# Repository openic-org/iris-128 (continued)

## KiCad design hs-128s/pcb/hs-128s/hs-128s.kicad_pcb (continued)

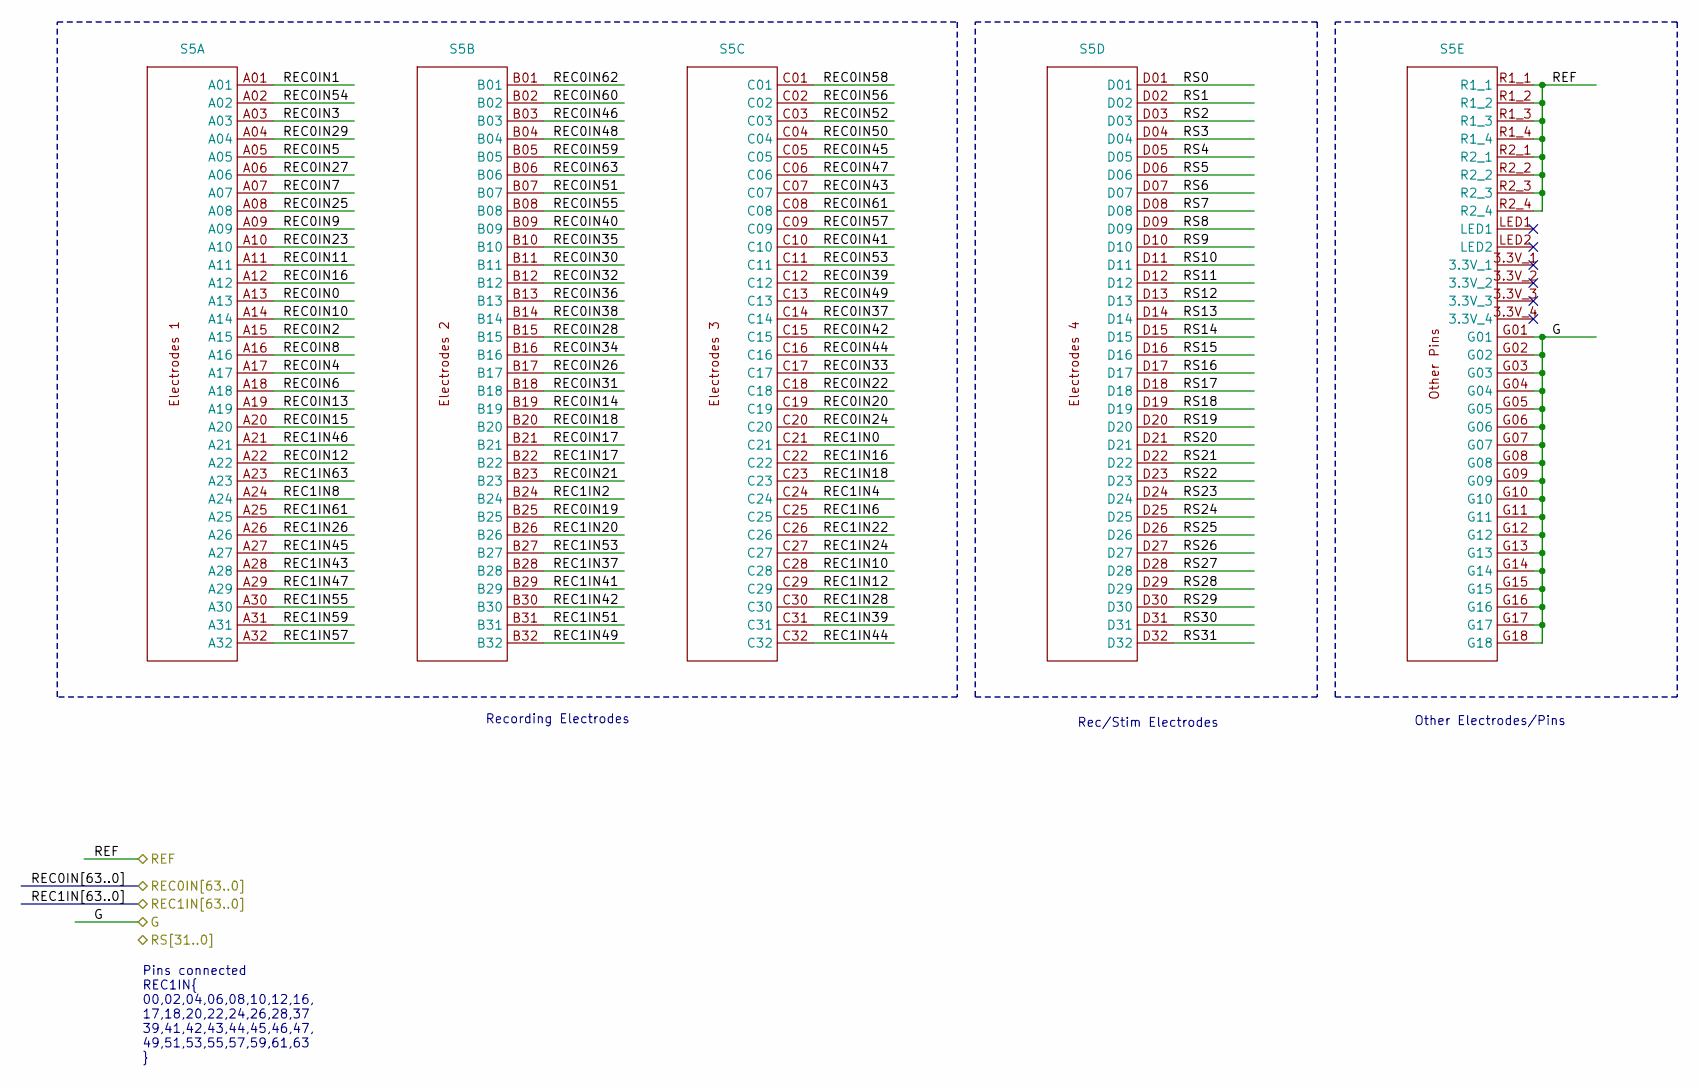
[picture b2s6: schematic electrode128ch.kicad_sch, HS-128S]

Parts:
S5: SAMTEC_SEAM8-20-S02.0-X-08-3_Cereplex; MPN SEAM8-20-S02.0-S-08-3

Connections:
/REC0IN0: S5.A13; also elsewhere on the board
/REC0IN1: S5.A01; also elsewhere on the board
/REC0IN2: S5.A15; also elsewhere on the board
/REC0IN3: S5.A03; also elsewhere on the board
/REC0IN4: S5.A17; also elsewhere on the board
/REC0IN5: S5.A05; also elsewhere on the board
/REC0IN6: S5.A18; also elsewhere on the board
/REC0IN7: S5.A07; also elsewhere on the board
/REC0IN8: S5.A16; also elsewhere on the board
/REC0IN9: S5.A09; also elsewhere on the board
/REC0IN10: S5.A14; also elsewhere on the board
/REC0IN11: S5.A11; also elsewhere on the board
/REC0IN12: S5.A22; also elsewhere on the board
/REC0IN13: S5.A19; also elsewhere on the board
/REC0IN14: S5.B19; also elsewhere on the board
/REC0IN15: S5.A20; also elsewhere on the board
/REC0IN16: S5.A12; also elsewhere on the board
/REC0IN17: S5.B21; also elsewhere on the board
/REC0IN18: S5.B20; also elsewhere on the board
/REC0IN19: S5.B25; also elsewhere on the board
/REC0IN20: S5.C19; also elsewhere on the board
/REC0IN21: S5.B23; also elsewhere on the board
/REC0IN22: S5.C18; also elsewhere on the board
/REC0IN23: S5.A10; also elsewhere on the board
/REC0IN24: S5.C20; also elsewhere on the board
/REC0IN25: S5.A08; also elsewhere on the board
/REC0IN26: S5.B17; also elsewhere on the board
/REC0IN27: S5.A06; also elsewhere on the board
/REC0IN28: S5.B15; also elsewhere on the board
/REC0IN29: S5.A04; also elsewhere on the board
/REC0IN30: S5.B11; also elsewhere on the board
/REC0IN31: S5.B18; also elsewhere on the board
/REC0IN32: S5.B12; also elsewhere on the board
/REC0IN33: S5.C17; also elsewhere on the board
/REC0IN34: S5.B16; also elsewhere on the board
/REC0IN35: S5.B10; also elsewhere on the board
/REC0IN36: S5.B13; also elsewhere on the board
/REC0IN37: S5.C14; also elsewhere on the board
/REC0IN38: S5.B14; also elsewhere on the board
/REC0IN39: S5.C12; also elsewhere on the board
/REC0IN40: S5.B09; also elsewhere on the board
/REC0IN41: S5.C10; also elsewhere on the board
/REC0IN42: S5.C15; also elsewhere on the board
/REC0IN43: S5.C07; also elsewhere on the board
/REC0IN44: S5.C16; also elsewhere on the board
/REC0IN45: S5.C05; also elsewhere on the board
/REC0IN46: S5.B03; also elsewhere on the board
/REC0IN47: S5.C06; also elsewhere on the board
/REC0IN48: S5.B04; also elsewhere on the board
/REC0IN49: S5.C13; also elsewhere on the board
/REC0IN50: S5.C04; also elsewhere on the board
/REC0IN51: S5.B07; also elsewhere on the board
/REC0IN52: S5.C03; also elsewhere on the board
/REC0IN53: S5.C11; also elsewhere on the board
/REC0IN54: S5.A02; also elsewhere on the board
/REC0IN55: S5.B08; also elsewhere on the board
/REC0IN56: S5.C02; also elsewhere on the board
/REC0IN57: S5.C09; also elsewhere on the board
/REC0IN58: S5.C01; also elsewhere on the board
/REC0IN59: S5.B05; also elsewhere on the board
/REC0IN60: S5.B02; also elsewhere on the board
/REC0IN61: S5.C08; also elsewhere on the board
/REC0IN62: S5.B01; also elsewhere on the board
/REC0IN63: S5.B06; also elsewhere on the board
/REC1IN0: S5.C21; also elsewhere on the board
/REC1IN2: S5.B24; also elsewhere on the board
/REC1IN4: S5.C24; also elsewhere on the board
/REC1IN6: S5.C25; also elsewhere on the board
/REC1IN8: S5.A24; also elsewhere on the board
/REC1IN10: S5.C28; also elsewhere on the board
/REC1IN12: S5.C29; also elsewhere on the board
/REC1IN16: S5.C22; also elsewhere on the board
/REC1IN17: S5.B22; also elsewhere on the board
/REC1IN18: S5.C23; also elsewhere on the board
/REC1IN20: S5.B26; also elsewhere on the board
/REC1IN22: S5.C26; also elsewhere on the board
/REC1IN24: S5.C27; also elsewhere on the board
/REC1IN26: S5.A26; also elsewhere on the board
/REC1IN28: S5.C30; also elsewhere on the board
/REC1IN37: S5.B28; also elsewhere on the board
/REC1IN39: S5.C31; also elsewhere on the board
/REC1IN41: S5.B29; also elsewhere on the board
/REC1IN42: S5.B30; also elsewhere on the board
/REC1IN43: S5.A28; also elsewhere on the board
/REC1IN44: S5.C32; also elsewhere on the board
/REC1IN45: S5.A27; also elsewhere on the board
/REC1IN46: S5.A21; also elsewhere on the board
/REC1IN47: S5.A29; also elsewhere on the board
/REC1IN49: S5.B32; also elsewhere on the board
/REC1IN51: S5.B31; also elsewhere on the board
/REC1IN53: S5.B27; also elsewhere on the board
/REC1IN55: S5.A30; also elsewhere on the board
/REC1IN57: S5.A32; also elsewhere on the board
/REC1IN59: S5.A31; also elsewhere on the board
/REC1IN61: S5.A25; also elsewhere on the board
/REC1IN63: S5.A23; also elsewhere on the board
/REF_ELEC: S5.R1_1, S5.R1_2, S5.R1_3, S5.R1_4, S5.R2_1, S5.R2_2, S5.R2_3, S5.R2_4; also elsewhere on the board
/RS0: S5.D01; also elsewhere on the board
/RS1: S5.D02; also elsewhere on the board
/RS2: S5.D03; also elsewhere on the board
/RS3: S5.D04; also elsewhere on the board
/RS4: S5.D05; also elsewhere on the board
/RS5: S5.D06; also elsewhere on the board
/RS6: S5.D07; also elsewhere on the board
/RS7: S5.D08; also elsewhere on the board
/RS8: S5.D09; also elsewhere on the board
/RS9: S5.D10; also elsewhere on the board
/RS10: S5.D11; also elsewhere on the board
/RS11: S5.D12; also elsewhere on the board
/RS12: S5.D13; also elsewhere on the board
/RS13: S5.D14; also elsewhere on the board
/RS14: S5.D15; also elsewhere on the board
/RS15: S5.D16; also elsewhere on the board
/RS16: S5.D17; also elsewhere on the board
/RS17: S5.D18; also elsewhere on the board
/RS18: S5.D19; also elsewhere on the board
/RS19: S5.D20; also elsewhere on the board
/RS20: S5.D21; also elsewhere on the board
/RS21: S5.D22; also elsewhere on the board
/RS22: S5.D23; also elsewhere on the board
/RS23: S5.D24; also elsewhere on the board
/RS24: S5.D25; also elsewhere on the board
/RS25: S5.D26; also elsewhere on the board
/RS26: S5.D27; also elsewhere on the board
/RS27: S5.D28; also elsewhere on the board
/RS28: S5.D29; also elsewhere on the board
/RS29: S5.D30; also elsewhere on the board
/RS30: S5.D31; also elsewhere on the board
/RS31: S5.D32; also elsewhere on the board
GND1: S5.G01, S5.G02, S5.G03, S5.G04, S5.G05, S5.G06, S5.G07, S5.G08, S5.G09, S5.G10, S5.G11, S5.G12, S5.G13, S5.G14, S5.G15, S5.G16, S5.G17, S5.G18; also elsewhere on the board

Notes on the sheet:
Pins connected REC1IN{ 00,02,04,06,08,10,12,16, 17,18,20,22,24,26,28,37 39,41,42,43,44,45,46,47, 49,51,53,55,57,59,61,63 }
Rec/Stim Electrodes
Other Electrodes/Pins
Recording Electrodes

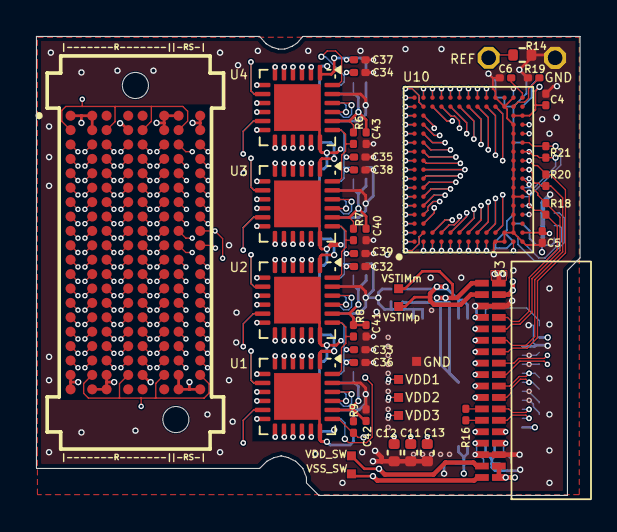
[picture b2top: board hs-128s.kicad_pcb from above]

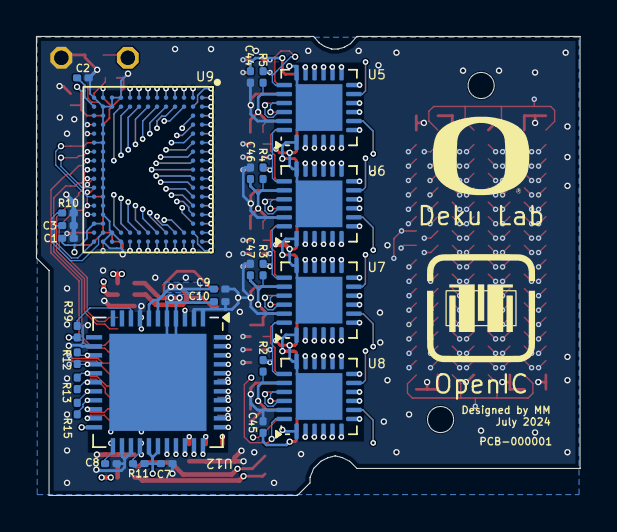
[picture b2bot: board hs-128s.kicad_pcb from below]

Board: 8 copper layers, 30.2 x 25.5 mm, 72 parts (27 on the bottom side), 223 nets.

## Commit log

2025-06-24 first commit.
